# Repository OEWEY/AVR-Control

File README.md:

# AVR-Control

## Scope:
- Create an interface between a Raspberry Pi and a Pioneer A-20 AVR receiver.
- This is done by sending IR-codes with an ATtiny85 to the IR-in jack based on GPIO states of the Raspberry Pi.

## Hardware:
The following components are required:
- an ATtiny85
- a NPN transistor such as the BC548
- a 10k pull-up resistor for the output signal (R1)
- a 2k2 resistor for limiting the base curreont of the transistor (R2)
- three jumper wires for connecting the Raspberry Pi to the ATtiny board
- some pin headers
- a 3.5mm audio jack (mono)

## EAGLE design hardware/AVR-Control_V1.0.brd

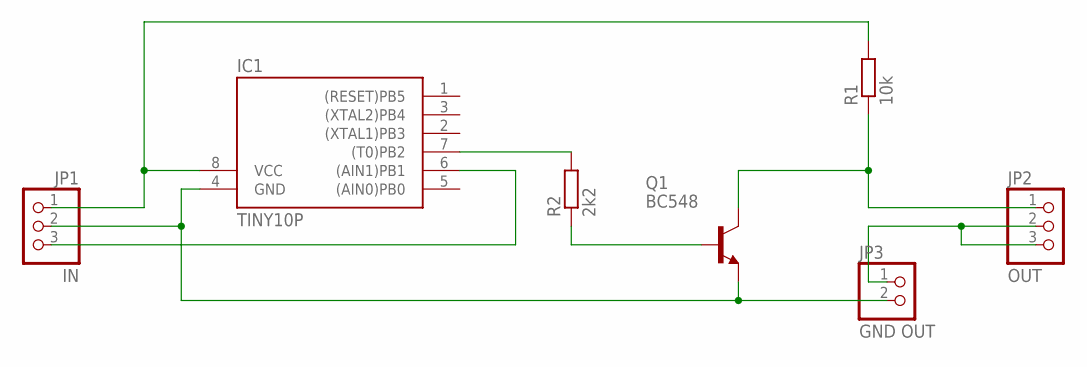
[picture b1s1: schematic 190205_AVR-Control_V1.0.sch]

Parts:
IC1: TINY10P; DIL08
JP1: IN; 1X03/90
JP2: OUT; 1X03/90
JP3: GND OUT; 1X02
Q1: BC548; TO92-EBC
R1: 10k; R1206
R2: 2k2; R1206

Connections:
ATTINY_OUT: IC1.7 ((T0)PB2), R2.2
BASE: Q1.B, R2.1
GND: IC1.4 (GND), JP1.2, JP3.2, Q1.E
GND_OUTPUT: JP2.2, JP2.3, JP3.1
SIG_IN: IC1.6 ((AIN1)PB1), JP1.3
SIG_OUT: JP2.1, Q1.C, R1.1
VCC: IC1.8 (VCC), JP1.1, R1.2

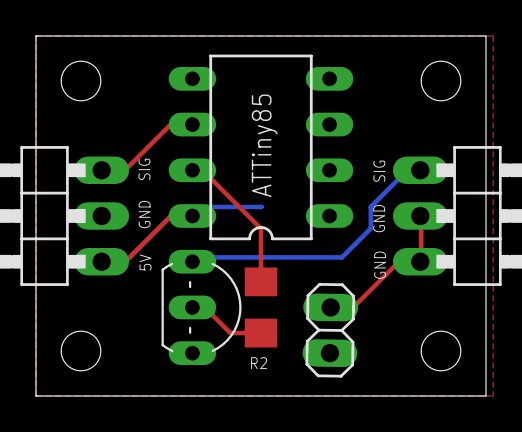
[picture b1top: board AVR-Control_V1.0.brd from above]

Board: 2 copper layers, 25.0 x 20.0 mm, 7 parts (1 on the bottom side), 7 nets.

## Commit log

2021-02-02 Add draft from 2019-02-05
2021-02-02 Update AVR_IR-in_Control_ATTiny85.ino (#1)
    * Update AVR_IR-in_Control_ATTiny85.ino
    * Update AVR_IR-in_Control_ATTiny85.ino
2021-02-02 Scope and hardware components added
2021-02-02 Rename 190205_AVR-Control_V1.0.b#1 to hardware/190205_AVR-Control_V1.0.b#1
2021-02-02 Rename 190205_AVR-Control_V1.0.brd to hardware/AVR-Control_V1.0.brd
2021-02-02 Rename 190205_AVR-Control_V1.0.b#1 to AVR-Control_V1.0.b#1
2021-02-02 Rename 190205_AVR-Control_V1.0.sch to hardware/190205_AVR-Control_V1.0.sch
